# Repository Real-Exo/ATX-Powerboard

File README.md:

A small board that allows controlling a standard ATX PC power supply in order to power other things. 
Onboard ON/OFF switch. External ON/OFF can be configured to be pulsed (push-button, for example) or latching (switch).
Do not change configuration jumper while board is running as that triggers a safety lockup (flashing diag LED).
Monitors PSU power good signal and turns PSU off when PWR_GOOD is not asserted, flashing diag LED.

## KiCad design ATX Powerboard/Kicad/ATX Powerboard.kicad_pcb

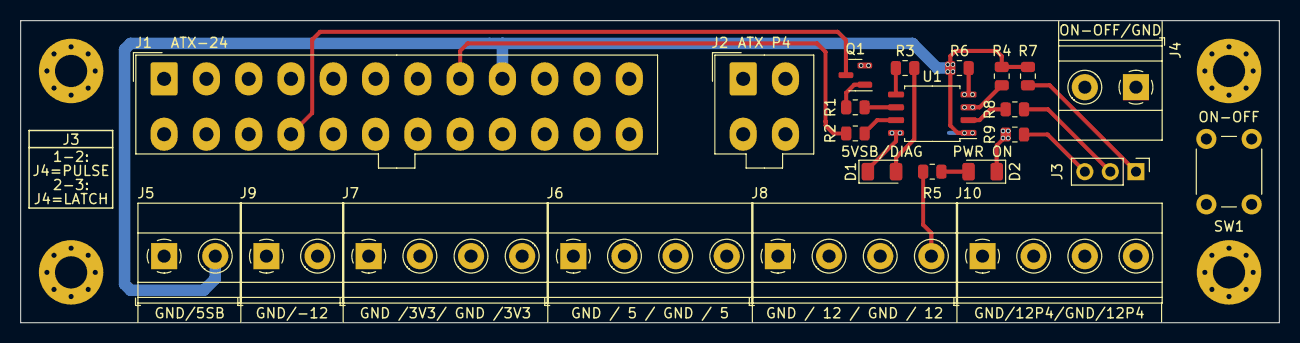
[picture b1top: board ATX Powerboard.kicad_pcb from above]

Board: 4 copper layers, 125.0 x 30.0 mm, 25 parts (1 on the bottom side), 21 nets.

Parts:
C1: 100n; C_0805_2012Metric
D1: 5VSB/DIAG; LED_1206_3216Metric
D2: PWR ON; LED_1206_3216Metric
J1: ATX-24; Molex_Mini-Fit_Jr_5566-24A_2x12_P4.20mm_Vertical
J2: ATX P4; Molex_Mini-Fit_Jr_5566-04A_2x02_P4.20mm_Vertical
J3: M/L; PinHeader_1x03_P2.54mm_Vertical
J4: ON-OFF/GND; TerminalBlock_Phoenix_MKDS-1,5-2-5.08_1x02_P5.08mm_Horizont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
J5: GND/5SB; TerminalBlock_Phoenix_MKDS-1,5-2-5.08_1x02_P5.08mm_Horizont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
J6: GND / 5 / GND / 5; TerminalBlock_Phoenix_MKDS-1,5-4-5.08_1x04_P5.08mm_Horizont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
J7: GND /3V3/ GND /3V3; TerminalBlock_Phoenix_MKDS-1,5-4-5.08_1x04_P5.08mm_Horizont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
J8: GND / 12 / GND / 12; TerminalBlock_Phoenix_MKDS-1,5-4-5.08_1x04_P5.08mm_Horizont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
J9: GND/-12; TerminalBlock_Phoenix_MKDS-1,5-2-5.08_1x02_P5.08mm_Horizont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
J10: GND/12P4/GND/12P4; TerminalBlock_Phoenix_MKDS-1,5-4-5.08_1x04_P5.08mm_Horizont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
Q1: BSS138; SOT-23
R1, R2, R4, R5, R6, R7, R8, R9: 10K; R_0805_2012Metric
R3: 3K3; R_0805_2012Metric
SW1: ON-OFF; SW_PUSH_6mm_H5mm
U1: PIC12C508A-ISM; SOIC-8_5.275x5.275mm_P1.27mm

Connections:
+3V3: J1.1 (+3.3V), J1.2 (+3.3V), J1.12 (+3.3V), J1.13 (+3.3V), J7.2, J7.4
+5V: J1.4 (+5V), J1.6 (+5V), J1.21 (+5V), J1.22 (+5V), J1.23 (+5V), J6.2, J6.4
+5V STDBY: C1.1, J1.9 (+5VSB), J5.2, R4.1, R6.1, R7.1, U1.1 (VDD)
+12P: J2.3, J2.4, J10.2, J10.4
+12V: J1.10 (+12V), J1.11 (+12V), J8.2, J8.4, R5.1
-12V: J1.14 (-12V), J9.2
GND: C1.2, D1.1 (K), D2.1 (K), J1.3 (GND), J1.5 (GND), J1.7 (GND), J1.15 (GND), J1.17 (GND), J1.18 (GND), J1.19 (GND), J1.24 (GND), J2.1, J2.2, J4.1, J5.1, J6.1, J6.3, J7.1, J7.3, J8.1, J8.3, J9.1, J10.1, J10.3, Q1.2 (S), R9.1, SW1.2, U1.8 (VSS)
M/L: R8.1, U1.2 (GP5)
unnamed: D1.2 (A), R3.2
unnamed: D2.2 (A), R5.2
unnamed: J1.16 (PS_ON#), Q1.3 (D)
unnamed: J1.8 (PWR_OK), R2.1
unnamed: J3.1, R7.2
unnamed: J3.2, R8.2
unnamed: J3.3, R9.2
unnamed: Q1.1 (G), R1.2
unnamed: R3.1, U1.5 (GP2)
unnamed: R4.2, SW1.1, U1.3 (GP4)
ON/OFF: J4.2, R6.2, U1.4 (GP3)
PSON: R1.1, U1.6 (GP1)
PWROK: R2.2, U1.7 (GP0)
